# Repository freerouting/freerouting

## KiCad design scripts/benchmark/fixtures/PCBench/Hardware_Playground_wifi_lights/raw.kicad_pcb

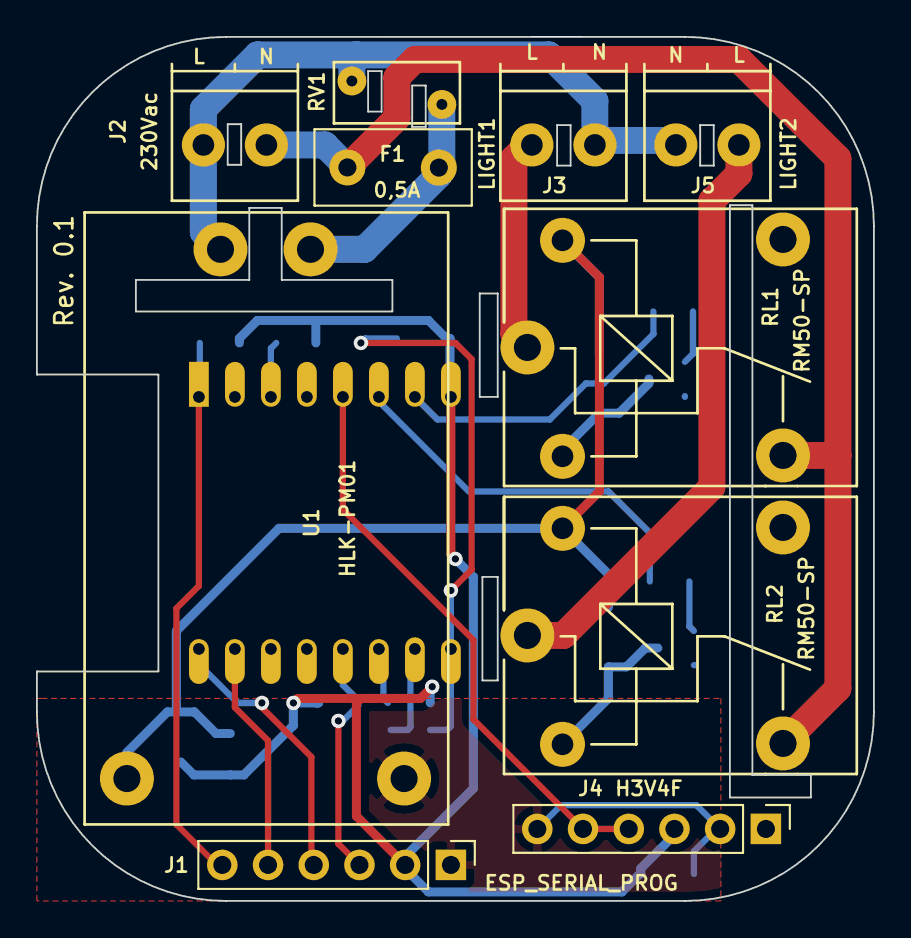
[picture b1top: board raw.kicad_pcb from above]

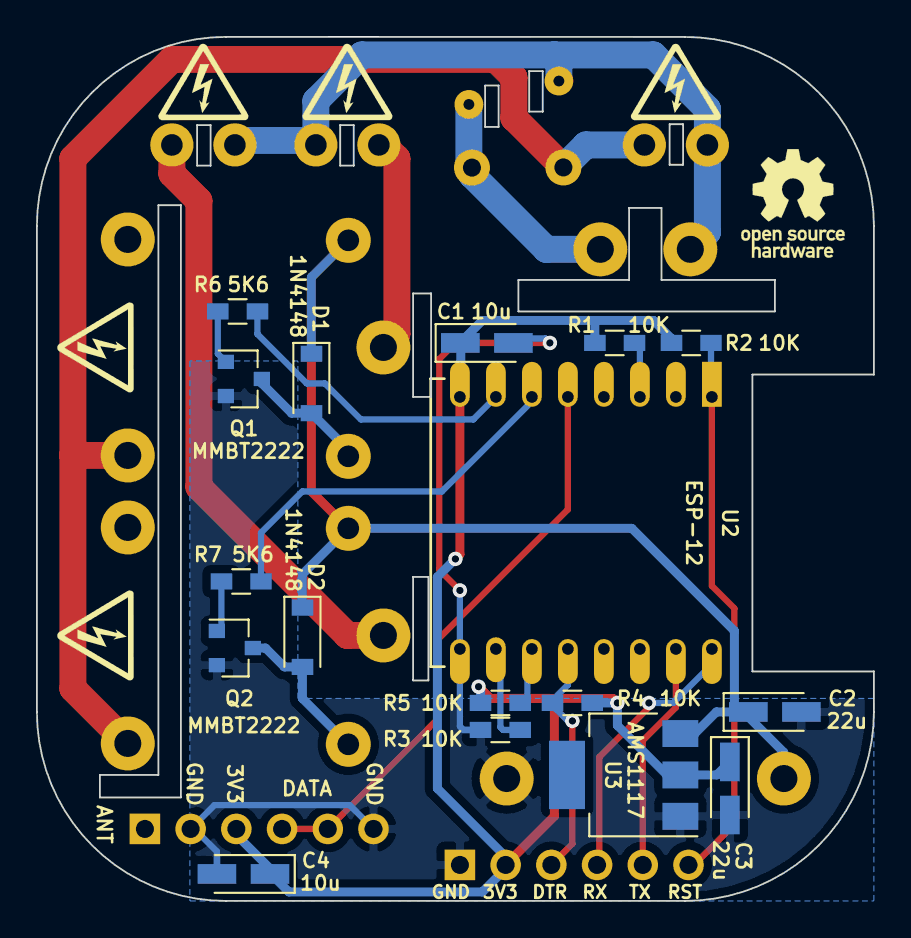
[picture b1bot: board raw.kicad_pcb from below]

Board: 2 copper layers, 46.5 x 48.0 mm, 27 parts (17 on the bottom side), 22 nets.

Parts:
C1, C4: 10u; CP_Tantalum_Case-A_EIA-3216-18_Wave
C2, C3: 22u; CP_Tantalum_Case-A_EIA-3216-18_Wave
D1, D2: 1N4148; D_SOD-123
F1: 0,5A; Fuse_TE5_Littlefuse-395Series
J1: ESP_SERIAL_PROG; Pin_Header_Straight_1x06_Pitch2.54mm
J2: 230Vac; TerminalBlock_Pheonix_PT-3.5mm_2pol
J3: LIGHT1; TerminalBlock_Pheonix_PT-3.5mm_2pol
J4: H3V4F; Pin_Header_Straight_1x06_Pitch2.54mm
J5: LIGHT2; TerminalBlock_Pheonix_PT-3.5mm_2pol
Q1, Q2: MMBT2222; SOT-23
R1, R2, R3, R4, R5: 10K; R_0603_HandSoldering
R6, R7: 5K6; R_0603_HandSoldering
RL1, RL2: RM50-SP; RM50_P
RV1: Varistor; RV_Disc_D7_W3.4_P5
U1: ESP-12
U2: HLK-PM01
U3: AMS1117; SOT-223

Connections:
+3V3: C1.1, C3.1, C4.1, J1.2, J4.3, R1.2, R2.2, R4.2, R5.2, U1.8, U3.2
+5V: C2.1, D1.1, D2.1, RL1.A1, RL2.A1, U2.3, U3.3
/433_RX_DATA: J4.4, J4.5, U1.5
/DTR: J1.3, R4.1, U1.12
/L: F1.1, J2.1, RL1.14, RL2.14
/N: J2.2, J3.1, J5.2, RV1.2, U2.2
/RELAY_CH1: R6.2, U1.7
/RELAY_CH2: R7.2, U1.6
/REL_SW1: J3.2, RL1.11
/REL_SW2: J5.1, RL2.11
/RESET: J1.6, R2.1, U1.1
/RX: J1.4, U1.16
/TX: J1.5, U1.15
GND: C1.2, C2.2, C3.2, C4.2, J1.1, J4.2, J4.6, Q1.2, Q2.2, R3.1, U1.9, U2.4, U3.1
unnamed: D1.2, Q1.3, RL1.A2
unnamed: D2.2, Q2.3, RL2.A2
unnamed: F1.2, RV1.1, U2.1
unnamed: Q1.1, R6.1
unnamed: Q2.1, R7.1
unnamed: R1.1, U1.3
unnamed: R3.2, U1.10
unnamed: R5.1, U1.11

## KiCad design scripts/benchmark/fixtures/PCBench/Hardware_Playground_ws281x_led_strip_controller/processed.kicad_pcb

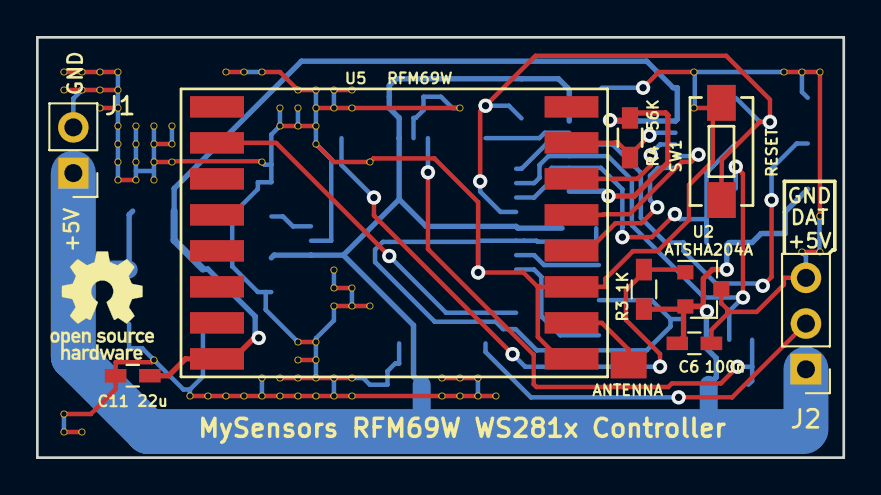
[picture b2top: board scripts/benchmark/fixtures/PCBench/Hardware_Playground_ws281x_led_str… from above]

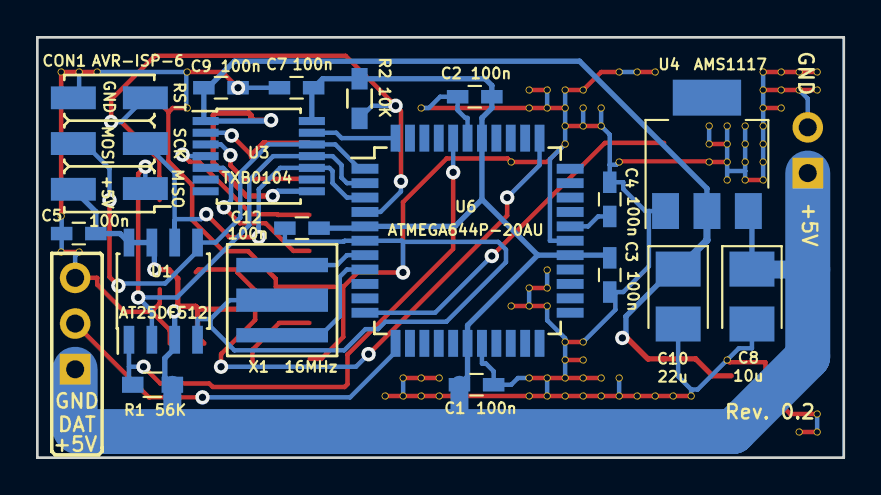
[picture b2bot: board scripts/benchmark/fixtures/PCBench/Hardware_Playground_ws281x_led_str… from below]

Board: 2 copper layers, 44.8 x 23.4 mm, 117 parts (18 on the bottom side), 20 nets.

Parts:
C1, C2, C3, C4, C5, C6, C7, C9, C12: 100n; C_0603_HandSoldering
C8: 10u; CP_Tantalum_Case-B_EIA-3528-21_Reflow
C10: 22u; CP_Tantalum_Case-B_EIA-3528-21_Reflow
C11: 22u; C_0603_HandSoldering
CON1: AVR-ISP-6; AVR_ISP_SMT_Small_02x03
J1: PWR; Pin_Header_Straight_1x02_Pitch2.54mm
J2: CTRL_OUT; Pin_Header_Straight_1x03_Pitch2.54mm
P1: ANTENNA; 1pin_smd_2mm
R1, R4: 56K; R_0603_HandSoldering
R2: 10K; R_0603_HandSoldering
R3: 1K; R_0603_HandSoldering
SW1: RESET; SW_SPST_EVQPE1
U1: AT25DF512; SOIC-8_3.9x4.9mm_Pitch1.27mm
U2: ATSHA204A; SOT-23
U3: TXB0104; TSSOP-14_4.4x5mm_Pitch0.65mm
U4: AMS1117; SOT-223
U5: RFM69W; RFM69HW_SMD_Handsoldering
U6: ATMEGA644P-20AU; TQFP-44_10x10mm_Pitch0.8mm
V10_2, V10_3, V10_21, V10_22, V11_2, V11_3, V11_22, V12_2, V12_3, V12_4, V13_2, V13_3, V13_4, V13_5, V13_6, V13_7, V13_8, V14_5, V14_6, V14_7, V14_8, V15_5, V15_6, V15_7, V15_8, V15_18, V16_5, V16_6, V16_7, V17_20, V18_20, V19_2, V19_20, V20_2, V20_20, V21_2, V21_7, V21_19, V21_20, V22_4, V22_5, V22_19, V22_20, V23_3, V23_4, V23_5, V23_17, V23_18, V23_19, V23_20, V24_3, V24_4, V24_5, V24_6, V24_17, V24_18, V24_19, V24_20, V25_3, V25_4, V25_13, V25_14, V25_15, V25_19, V25_20, V26_3, V26_4, V26_14, V26_15, V26_19, V26_20, V27_7, V27_15, V31_19, V31_20, V32_4, V32_19, V32_20, V33_19, V33_20, V34_20, V45_2, V45_4, V50_2, V51_2, V51_12, V52_2, V52_10, V52_12: AUTO_VIA; VIA_MATRIX
X1: 16MHz; ZTTCS-3

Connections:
+3V3: C9.2, C10.1, C11.1, R4.2, U3.1, U3.8, U4.2, U5.8
+5V: C1.2, C2.2, C3.2, C5.1, C6.1, C7.1, C8.1, C12.2, CON1.2, J1.1, J2.1, R1.2, R2.1, R3.2, U1.3, U1.7, U1.8, U2.2, U3.14, U4.3, U6.5, U6.17, U6.27, U6.38
/ATSHA204A: R3.1, U2.1, U6.34
/D_OUT: J2.2, U6.12
/MISO: CON1.1, U1.2, U3.11, U6.2
/MOSI: CON1.4, U1.5, U3.12, U6.1
/RFM69W_INT: U5.2, U6.11
/RFM69W_SS: U3.13, U6.44
/RST: CON1.5, R2.2, SW1.1, U6.4
/SCK: CON1.3, U1.6, U3.10, U6.3
/SPI_FLASH_SS: R1.1, U1.1, U6.40
GND: C1.1, C2.1, C3.1, C4.1, C5.2, C6.2, C7.2, C8.2, C9.1, C10.2, C11.2, C12.1, CON1.6, J1.2, J2.3, SW1.2, U1.4, U2.3, U4.1, U5.9, U5.11, U6.6, U6.18, U6.28, U6.39, V10_2.1, V10_3.1, V10_21.1, V10_22.1, V11_2.1, V11_3.1, V11_22.1, V12_2.1, V12_3.1, V12_4.1, V13_2.1, V13_3.1, V13_4.1, V13_5.1, V13_6.1, V13_7.1, V13_8.1, V14_5.1, V14_6.1, V14_7.1, V14_8.1, V15_5.1, V15_6.1, V15_7.1, V15_8.1, V15_18.1, V16_5.1, V16_6.1, V16_7.1, V17_20.1, V18_20.1, V19_2.1, V19_20.1, V20_2.1, V20_20.1, V21_2.1, V21_7.1, V21_19.1, V21_20.1, V22_4.1, V22_5.1, V22_19.1, V22_20.1, V23_3.1, V23_4.1, V23_5.1, V23_17.1, V23_18.1, V23_19.1, V23_20.1, V24_3.1, V24_4.1, V24_5.1, V24_6.1, V24_17.1, V24_18.1, V24_19.1, V24_20.1, V25_3.1, V25_4.1, V25_13.1, V25_14.1, V25_15.1, V25_19.1, V25_20.1, V26_3.1, V26_4.1, V26_14.1, V26_15.1, V26_19.1, V26_20.1, V27_7.1, V27_15.1, V31_19.1, V31_20.1, V32_4.1, V32_19.1, V32_20.1, V33_19.1, V33_20.1, V34_20.1, V45_2.1, V45_4.1, V50_2.1, V51_2.1, V51_12.1, V52_2.1, V52_10.1, V52_12.1, X1.2
unnamed: C4.2, U6.29
unnamed: P1.1, U5.10
unnamed: R4.1, U3.2, U5.15
unnamed: U3.3, U5.14
unnamed: U3.4, U5.13
unnamed: U3.5, U5.12
unnamed: U6.7, X1.1
unnamed: U6.8, X1.3

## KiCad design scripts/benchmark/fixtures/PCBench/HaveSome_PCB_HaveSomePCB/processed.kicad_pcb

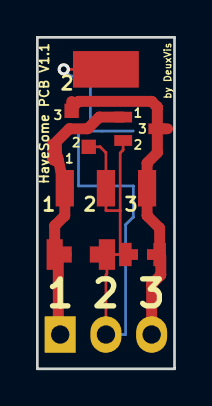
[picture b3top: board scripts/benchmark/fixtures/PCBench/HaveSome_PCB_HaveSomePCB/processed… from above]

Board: 2 copper layers, 7.6 x 18.4 mm, 8 parts (0 on the bottom side), 3 nets.

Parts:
PINS1: CONN_01X03; Pin_Header_Straight_1x03
SMD402: R0402; R_0402
SMD603: R0603; R_0603
SMD805: R0805; R_0805
SMD1206: R1206; R_1206
SOT23: APE8865NL-33-HF-3; SOT-23
SOT223: LD1117S33CTR; SOT-223
SOT323: BFR92; SOT-323

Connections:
unnamed: PINS1.1, SMD603.2, SMD1206.2, SOT23.1, SOT223.1, SOT323.1
unnamed: PINS1.2, SMD402.2, SMD603.1, SMD805.2, SMD1206.1, SOT23.2, SOT223.2, SOT223.4, SOT323.2
unnamed: PINS1.3, SMD402.1, SMD805.1, SOT23.3, SOT223.3, SOT323.3
